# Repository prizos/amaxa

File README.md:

# amaxa

A mechatronics driver board for motors and inverters — small motors, servos,
compressors, and up through high-power drives.

The architecture is one **digital control board** that generates every hard
real-time signal, soldered onto **one analog power board** at a time. There are
N power-board types, from a few tens of milliamps to hundreds of amps, AC or DC;
the control board is the same in each case. It does the control in real-time
software on a single fast Arm core rather than in dedicated hardware, which is
what keeps the silicon cheap.

**Nothing here is finished.** What exists is the groundwork: the research that
chose the parts, a firmware build that runs in an emulator, and a board design
pipeline proven end to end on a deliberately trivial board.

## What is here

| | |
|---|---|
| [`docs/research/`](docs/research/README.md) | Why the MCU, the power-board interface and the design toolchain are what they are |
| [`firmware/`](firmware/README.md) | Bare-metal STM32H743, GCC through Bazel, running under Renode in CI |
| [`hw/`](hw/README.md) | Boards designed as code: SKiDL, KiCad, ngspice, all gated in CI |

## The boards

### `hw/cpu1` — the control board

[`hw/cpu1`](hw/cpu1/README.md) is the real one: an STM32H743ZIT6 that
generates every hard real-time signal — PWM for two three-phase bridges, ADC
sampling synchronised to it, and a hardware trip that stops the outputs
without firmware — and hands all of it to a power board across two pin
headers. 130 × 110 mm, six layers, 272 parts.

It is drawn, routed and checked: 203 checks, DRC clean with nothing
unconnected, gerbers for all six layers, and a build that reaches nothing over
the network. Its trip chain measures 40.5 ns against a 50 ns budget, and every
figure in that sum is derived from the netlist, the routed copper or a
datasheet page committed as an evidence crop.

**[`DESIGN-REVIEW.md`](hw/cpu1/DESIGN-REVIEW.md) is the account of what it is
and does**, including a section on what is assumed rather than measured. What
it has not had is a power board to talk to, or a reflow oven.

### `hw/led12` — the board that proved the pipeline

[`hw/led12`](hw/led12/README.md) is a 12 V LED board with no processor. Press a
button, four LEDs light. Its only purpose was to prove the pipeline before the
control board depended on it.

Neither board has been fabricated. What is proven is the pipeline.

## Getting started

Both halves are self-contained and pin everything they use by checksum.

```sh
make -C firmware          # build the firmware
make -C firmware sim      # run it under Renode

make -C hw tools          # pinned uv, Python and the design virtualenv
make -C hw check          # build the board and run the design checks
```

`hw/` also needs KiCad 9 and ngspice from your package manager;
[`hw/README.md`](hw/README.md) says why the version matters.

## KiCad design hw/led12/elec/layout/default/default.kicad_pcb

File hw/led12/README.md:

# led12 — 12 V LED board

A deliberately small board with no processor. Press the button, four LEDs light.
That is the whole function. Its job is to prove the design pipeline end to end
before any of it is trusted with the STM32H743 control board.

| Top | Bottom |
|---|---|
|  |  |

50 × 40 mm, two layers, 30 parts, and a ground pour on the back. **It has never
been fabricated.**

## The circuit

```
                       D ┌────┐ S
  12V in ──[fuse 1A]─────┤ Q1 ├────┬───────┬── 12V
                         └─┬──┘    │       │
                           G      TVS   47uF + 100nF
                    100k ──┤ D6           │
                     GND ──┴──┘           ├── 4 x (2k2 + LED) cathodes
                                          │
  button ──[10k]──┬── N-FET gate          └── LDO 3V3 ── 3k3 load
                  │
             1uF ─┤ 100k ──┤ D7   N-FET drain sinks LED_RETURN
                  └── GND ──┘
```

The input is fused, reverse-polarity protected by a P-FET, and clamped by a TVS.
Pressing the button charges the gate of a low-side N-FET through an RC network,
which sinks the return of four LED branches. A linear regulator provides a 3.3 V
rail with a fixed load so it can be measured. Four test pads expose 12 V, 3.3 V,
ground and the gate.

Three things are less obvious than they look:

- **Q1's drain faces the supply.** A P-MOSFET's body diode has its anode on the
  drain, so that is the orientation in which it blocks a reversed input. Source
  to the supply reads more naturally, is how a high-side load switch is drawn,
  works perfectly on the bench — and leaves the board unprotected.
- **D6 and D7 are 15 V Zeners clamping each FET's gate.** The TVS clamps at
  23.2 V, and both FETs are ±20 V gate-source, so without these a surge takes
  each gate past its rating. 15 V is the only window: above the 13.2 V the rail
  may reach, below the 20 V the FETs allow.
- **The TVS stands off 14 V, not 12.** The rail is specified to 13.2 V, and a
  TVS above its stand-off voltage leaks — more so cold, because avalanche
  breakdown has a positive temperature coefficient. A 12 V part made the
  protection a load at high line.

## Bill of materials

Generated at `build/bom.csv` by `make build`, and published with every CI run.
Every part is verified against the distributor, with a review note in
`parts/<LIB>/<LIB>.md` recording the datasheet it was read from, what was
rejected and why, and what still needs a person to confirm.

**Four of those notes are still marked "Needs a human eye"**, all of them pin
mappings taken from footprint geometry or distributor symbol data rather than
from a manufacturer drawing. One says in plain words that the board may short
3V3 to GND if its assumption is wrong. `checks/test_parts.py` tracks the list;
clearing it is a precondition for ordering.

## What the gates caught

Eight real defects so far, and the split is the interesting part.

**Five came from the gates as they were built:** a bulk capacitor that was a
6.3 V part on a 12 V rail; a reverse-polarity FET rated ±8 V gate-source in a
circuit that puts 13.2 V across it; LED series resistors dissipating 104 % of
their rating, because 680 Ω is a 5 V habit; a regulator rated 15 V behind a TVS
clamping at 19.9 V; and the TVS itself fitted backwards.

**Three came from an adversarial review** that went looking for what the gates
could *not* see — and all three were in the board, not the checks. The
reverse-polarity FET was wired source-to-supply, so its body diode conducted
under reverse polarity: a two-diode short from ground to the reversed input,
simulated at 69 A. The TVS stood off 12 V on a 13.2 V rail. And neither FET's
gate survived the clamp.

The lesson worth carrying is the second one. The check meant to catch a part
fitted backwards was *holding the FET backwards*, because its expected value was
a hand-written table of what we believed. Correcting the board turned that check
red. Expected values are derived from the netlist now, wherever they can be.

## DRC

Zero errors, against both the PCBWay fab limits and the board's own rules. Nine
warnings remain, and neither group is about the design:

- **Seven `lib_footprint_mismatch`**, one per rotated footprint — R1–R4, Q1, D6,
  D7. `pcbnew` re-normalises a rotated footprint when it fills the pours. The
  count moved from four to seven when three parts were rotated, which is how the
  cause was established.
- **Two silkscreen**, on `tp_gnd`'s reference. Two more were fixed by moving the
  label off its own pad outline; these last two are not positional — every
  offset tried leaves exactly them — and cannot be chased from the DRC report,
  whose JSON gives a reference field's position as twice the offset written.

## The files

| | |
|---|---|
| `led12.py` | the circuit — the only file that knows SKiDL |
| `parts.py` | every part as data — symbol, footprint, part number, datasheet figures |
| `layout.py` | the board: size, placement, routing, vias and the ground pour |
| `board.kicad_pro` | netclasses and the clearances DRC enforces |
| `rules.kicad_dru` | design intent: track widths, clearances |
| `sim/` | ngspice decks, device models and the bands each measurement must meet |
| `parts/<LIB>/` | footprint, and the review note recording what a human checked |
| `reference/` | the board as the previous design source last built it, frozen |

How to change any of it, and what each gate does, is in
[`../README.md`](../README.md).

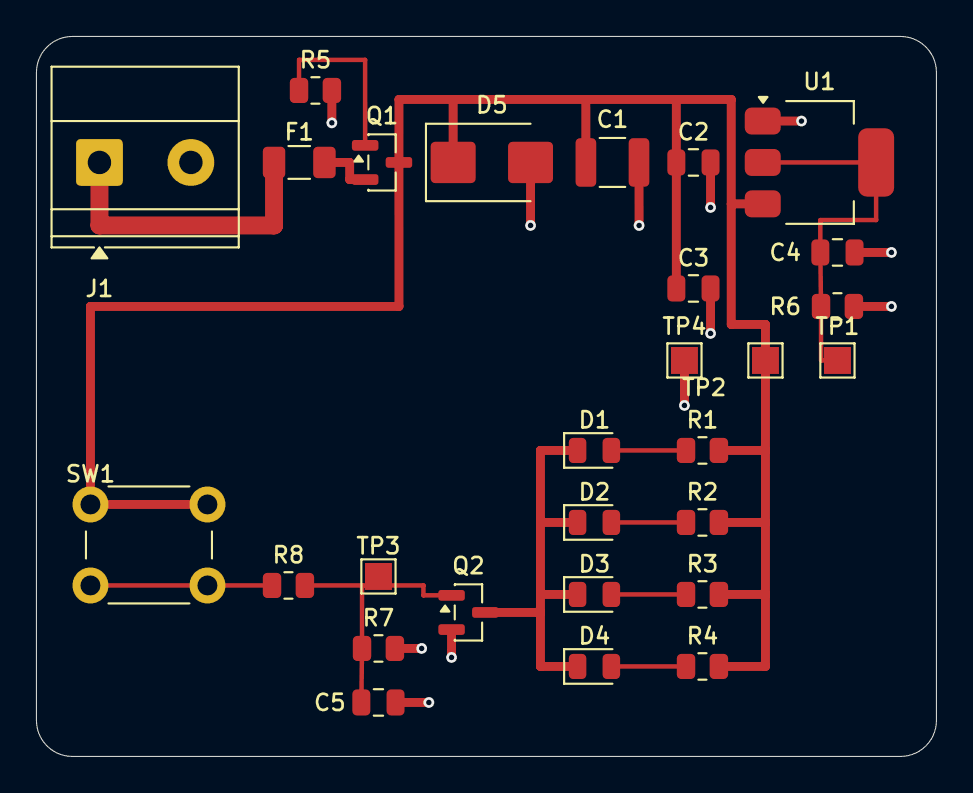
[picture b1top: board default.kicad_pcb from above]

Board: 2 copper layers, 50.0 x 40.0 mm, 28 parts (0 on the bottom side), 13 nets.

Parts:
C1: 47µF ±20%; C_1210_3225Metric
C2: 100nF ±10%; C_0805_2012Metric
C3, C5: 1µF ±10%; C_0805_2012Metric
C4: 10µF ±20%; C_0805_2012Metric
D1, D2, D3, D4: LED_0805_2012Metric
D5: Vf {ℝ+}V; D_SMB
F1: It 1A; Fuse_1206_3216Metric
J1: TerminalBlock_Phoenix_MKDS-1,5-2-5.08_1x02_P5.08mm_Horizont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
Q1: Vgs ℝ+V; SOT-23
Q2: Vgs 1.75V; SOT-23
R1, R2, R3, R4: 2.2kΩ ±1%; R_0805_2012Metric
R5, R7: 100kΩ ±1%; R_0805_2012Metric
R6: 3.3kΩ ±1%; R_0805_2012Metric
R8: 10kΩ ±1%; R_0805_2012Metric
SW1: SW_PUSH_6mm
TP1, TP2, TP3, TP4: TestPoint_Pad_1.5x1.5mm
U1: SOT-223-3_TabPin2

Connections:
3V3: C4.1, R6.1, TP1.1, U1.2
12V: C1.1, C2.1, C3.1, D5.1, Q1.3, R1.1, R2.1, R3.1, R4.1, SW1.1, TP2.1, U1.3
BTN: R8.1, SW1.2
GATE: C5.1, Q2.1, R7.1, R8.2, TP3.1
GND: C1.2, C2.2, C3.2, C4.2, C5.2, D5.2, J1.2, Q2.2, R5.2, R6.2, R7.2, TP4.1, U1.1
LED_A: D1.2, R1.2
LED_RETURN: D1.1, D2.1, D3.1, D4.1, Q2.3
RPP_GATE: Q1.1, R5.1
VIN_FUSED: F1.2, Q1.2
VIN_RAW: F1.1, J1.1
leds[1]-LED_A: D2.2, R2.2
leds[2]-LED_A: D3.2, R3.2
leds[3]-LED_A: D4.2, R4.2
